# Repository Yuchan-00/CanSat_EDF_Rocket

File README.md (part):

<h1 align="center">CanSat EDF Rocket</h1>

<p align="center"><b>한국어</b> · <a href="README.en.md">English</a></p>

<p align="center">
  90 mm 덕티드팬(EDF) 하나로 캔위성을 싣고 올라가는 3D 프린트 발사체,<br>
  그리고 같은 추진 모듈로 만든 가벼운 수직 이착륙(VTOL) 기체
</p>

<p align="center">

  <br>
  <sub>왼쪽: 로켓 구성(탄도 발사 + 캔위성 사출) · 오른쪽: VTOL 배터리 구성. CadQuery 형상을 PyVista(VTK)로 그린 렌더(색은 화면용), 2026-11-04.</sub>
</p>

로켓은 수직으로 올라가 모터를 끄고, 정점에서 노즈콘을 열어 캔위성을 내보낸 뒤 자체 낙하산으로 내려옵니다.
VTOL은 같은 추진·흡입 모듈에 짧은 전자부를 얹은 시험용 기체로, 배터리·유선·하이브리드 세 가지 전원 구성이 있습니다.
**2026-11-05 사용자 결정: 앞으로 배터리 구성만 씁니다.** 유선·하이브리드는 지우지 않았지만 캐리어 PCB rev 2c의 로직 배터리(1S, 6S 팩 −x 면)와 상단 캡 스위치로는 더 맞추지 않습니다. 로직 전원 부품의 질량은 사용자가 나중에 정합니다(`configs.vtol.logic_power.in_flight_mass_model` = false; [docs/v0.9_하드웨어_변경.md](docs/v0.9_하드웨어_변경.md) 19장).
자세는 배기구의 베인 4개(MG90S 직접 구동)로 잡고, 비행 계산은 모두 ATmega128A 칩 4개가 합니다.

> **실물 비행·추력 시험 전입니다.** 아래 숫자는 CAD, 슬라이서, 시뮬레이션에서 나온 값입니다.

## 한눈에 보기

| 항목 | 값 | 종류 | 근거 |
|---|---|:-:|---|
| 로켓 구성 질량 | **2,599.2 g** | M | `cad/exports/cadquery_report.json` |
| VTOL 질량 (배터리 / 유선 / 하이브리드) | **1,653.7 / 1,405.8 / 1,526.8 g** | M | `cadquery_report_vtol*.json` |
| 몸통 | Ø120 mm, 벽 1.2 mm | 설계 | `params.json` `body` |
| 높이 (로켓 / VTOL 배터리 / 유선·하이브리드) | 856.3 / 492.5 / 500.3 mm (발사대 제외; VTOL 배터리는 2026-11-05 스위치 보호 칼라 포함) | 설계 | CadQuery 보고서 `vehicle_h_mm` |
| 추진 | 90 mm 12엽 EDF, 6S, 100 A ESC | 부품 | [예산안](docs/budget/예산안.md) |
| EDF 추력 | 2.14–3.09 kgf (22.2 V) - **아직 재지 않음** | A | 3.09 = 판매자 추력표(대리값), 2.14 = 설계 하한(배터리 VTOL T/W 1.3), `params.json`. 판정 기준 안에서 날려면 약 2.6 kgf 이상 필요([결과 문서](docs/v0.9_시뮬레이션_제어_결과.md)) |
| 비행 컴퓨터 | ATmega128A × 4 (NAV · FCU · COM · GNS), 16 MHz, 250 Hz 제어 틱 | 설계 | `params.json` `flight_computer` |
| 예산 (로켓 / VTOL 배터리) | 421,232원 / 375,192원 | M + A | 2026-10-13 판매가, 추정 줄 일부 ([로켓](docs/budget/예산안.md), [VTOL](docs/budget/예산안_vtol.md)) |
| 출력 시간 (로켓 / VTOL) | 47 h 29 min / 34 h 46 min | M + A | Bambu Studio 슬라이스, 로고 퍼지량은 가정값 ([임시 출력 계획](cad/exports/print/provisional_v09_cadquery/print_plan_provisional.md): CadQuery STL 슬라이스, Fusion 실행 전) |

<sub>M = 도구로 잰 값(CadQuery, 슬라이서) · E = 추정 · A = 가정(아직 재지 않은 입력) · 설계 = `params.json` 입력값 · 부품 = 예산안의 구매 부품 사양. 질량은 출력 부품을 슬라이서 값으로 넣은 CAD 합계이고, 일부 전자부품 질량은 가정값입니다. 로켓 출력 시간은 발사대 포함.</sub>

## 갤러리

|  |  |  |  |
|:-:|:-:|:-:|:-:|
| <sub>로켓 · 2,599.2 g</sub> | <sub>VTOL 배터리 · 1,653.7 g</sub> | <sub>VTOL 유선 · 1,405.8 g</sub> | <sub>VTOL 하이브리드 · 1,526.8 g</sub> |

|  |  |
|:-:|:-:|
| <sub>로켓 구성: 외관과 1/4 잘라낸 내부 (캔위성 350 g, 낙하산, EDF, 배터리)</sub> | <sub>VTOL 구성: 낙하산·캔위성을 빼고 짧은 전자부를 얹은 기체</sub> |
|  |  |
| <sub>직접 구동 베인 단면: 서보 축과 베인 축이 한 선 위, 나사 없는 혼 소켓</sub> | <sub>같은 베인의 분해도</sub> |
|  |  |
| <sub>모터 전원선 통로 단면 (시계 장착, 몸통 밖 블리스터)</sub> | <sub>통로의 여유 범위: 재지 않아도 맞게 설계한 범위 (출구 각도 0–360°, 선 지름 3.6–4.3 mm)</sub> |
|  |  |
| <sub>로켓 옆모습: 로고는 전자부 모듈 양쪽(67° / 293°)</sub> | <sub>유선 전원 준비형 VTOL (배터리 없는 유선, 하이브리드)</sub> |

<sub>모든 그림은 CadQuery 형상의 렌더입니다. 전자부품은 외곽 상자로, 선·폼·나사 일부는 그림용으로 그렸습니다.</sub>

## YUCHAN 로고

<p align="center">
  <br>
  <sub>① 후보 4개 - 왼쪽 위부터 launch, extended, retro, patch. 사용자가 <b>launch</b>를 골랐습니다.</sub>
</p>
<p align="center">
  <br>
  <sub>② 기체 축을 따라 세로로 넣도록 다듬은 최종 모양 (펼친 크기 121.0 × 18.4 mm)</sub>
</p>
<p align="center">
  <br>
  <sub>③ 다듬기 전(위)과 후(아래) 확대 비교, 2 mm 격자</sub>
</p>

|  |  |
|:-:|:-:|
| <sub>④ 기체 위: 로켓 전자부 모듈 양쪽</sub> | <sub>④ 기체 위: VTOL 전자부 모듈 양쪽</sub> |

* **찍는 방법**: P2S + AMS 2색 상감. 흰 몸통(PLA Matte Ivory White 11100)의 바깥 벽 한 줄(0.42 mm)만 주황(Mandarin Orange 11300)으로, 튀어나오지 않습니다.
* **자리**: 전자부 모듈 방위 67° / 293°, 아래에서 위로 읽음. 형상 검사 C36 PASS (창·슬롯·구멍에서 3 mm 이상, 가장 가는 획 2.20 mm).
* **AMS 비용 (슬라이서 M, 퍼지량 150 / 210 mm³는 가정 A)**: 색 바꿈 576번, 출력 +14 h 23–26 min, 버리는 양 180.4 g.
* 자세한 내용: [하드웨어 변경 문서 18장](docs/v0.9_하드웨어_변경.md), [제작 가이드 2장](docs/제작가이드.md).

## 개발 과정

**v0.6.3 → v0.8.1 (2026-10-13 ~ 10-21)** - 예산판 로켓을 Fusion 360 스크립트와 CadQuery 두 프로그램으로 따로 모델링해 서로 확인했습니다. v0.8.1에서 GPS 위치 유지를 맡는 네 번째 칩(GNS)을 더했습니다.

|  |  |
|:-:|:-:|
| <sub>Fusion 360 스크립트 v0.6.3 실행 결과 (2026-10-20, 컴포넌트 41개)</sub> | <sub>v0.8.1 GNS 보드 배치 (CadQuery 트윈 그림)</sub> |

**v0.9 (2026-10-28)** - 가벼운 VTOL 구성, 직접 구동 베인, 제어 라운드(C1–C7), 검토 수정 라운드(F1–F10)와 유선 전원 규칙(T1–T6). 바뀔 때마다 이전 / 이후를 같은 조건의 시뮬레이션으로 나란히 비교했습니다.

<p align="center">
  <br>
  <sub><b>시뮬레이션 (실제 비행 영상 아님), 2배속.</b> 같은 강한 소용돌이 바람에서 v0.8.1 로켓 적층(왼쪽)은 회전이 커져 비상정지하고 낙하산을 펼치고, v0.9 VTOL(오른쪽)은 계속 비행합니다.
  기체·시뮬레이션 모델·제어가 모두 달라서 차이 전부를 제어 변경의 효과로 볼 수는 없습니다. 영상 속 기체는 흰색 도색 전의 검정판이고, 질량은 영상을 만들 때의 값입니다.</sub>
</p>

<p align="center">
  <br>
  <sub><b>시뮬레이션, 실시간.</b> 배터리 없는 유선 VTOL이 실내에서 1.5 m까지 떠올라 호버링합니다. 사람 모형은 크기 비교용입니다. 영상 속 기체는 흰색 도색 전의 검정판입니다.</sub>
</p>

**모터선 통로 (2026-10-28 ~ 11-04)** - 처음 두 판은 모터선 출구를 가정했고, 10-29에 실물 사진으로 출구를 확인했습니다. 11-03에는 어느 각도로 나와도 재지 않고 맞는 설계로 바꿨습니다: EDF를 돌려 선 묶음을 통로 하나에 맞추고, 장착 탭은 둘레의 키웨이 25개 중 가까운 곳에 들어갑니다(시계 장착).

<p align="center">
  <br>
  <sub>왼쪽부터 10-28 처음 → 10-28 수정 → 10-29 실물 사진 기준 출구 → 시계 장착(11-03 설계, 11-04 수정 라운드 뒤, 검정) → 11-04 흰색. 1/4 잘라낸 단면.</sub>
</p>

|  |  |
|:-:|:-:|
| <sub>실물 EDF (2026-10-29): 모터선 묶음이 나오는 자리를 이 사진으로 정했습니다</sub> | <sub>흰색 도색 직전의 로켓 (2026-11-04 오전, 검정 PLA). 위 갤러리가 지금 모습입니다</sub> |

## 아비오닉스 캐리어 PCB와 로직 전원 (2026-11-04 ~ 11-05)

VTOL의 칩 4개, 센서, 무선, 로거를 한 장에 올린 캐리어 PCB를 KiCad 10(kicad-cli)과 Freerouting으로 만들었습니다. **만들거나 전원을 넣어 본 적은 없습니다(NOT_VERIFIED).**

|  |  |
|:-:|:-:|
| <sub>캐리어 PCB rev 2c: 76 × 70 mm 4층, ATmega128A × 4, ESP-12E (kicad-cli 렌더)</sub> | <sub>같은 보드 윗면 (kicad-cli 렌더)</sub> |

<p align="center">
  <br>
  <sub>회로도 8장 (전원, NAV, FCU, COM, GNS, 레벨 시프터, 커넥터, 최상위)</sub>
</p>

* **검사 (M, kicad-cli 10.0.6)**: ERC 오류 0 · 경고 0, DRC 오류 0 · 경고 0 · 미연결 0 · 회로도 불일치 0. 부품 162개(실장 152), 넷 100개.
* **사용자가 정한 부품**: BMP280, GY-521, NEO-7M(리드만), 무선 ESP-12E(LoRa PLM100 대신, 2026-11-05), 로직 배터리 1S 4200 mAh(디바이스마트 16021596). 부품은 모두 JLCPCB(LCSC) 또는 디바이스마트에서 찾은 것만 썼습니다.
* **고쳐 온 과정**: rev 1(PLM100 + 2S, 2층)은 독립 검토에서 디커플링·크리스털·실크·GND 문제가 나와 다시 만들었습니다. rev 2는 2층으로는 배선이 끝나지 않아(미연결 63) 4층으로 바꿨고, 쓰지 않는 5번째 칩 자리를 뺐습니다. rev 1은 [`pcb/vtol_carrier/archive/`](pcb/vtol_carrier/archive/)에 있습니다.
* **로직 전원 (CAD)**: 1S 팩은 6S 팩 −x 면(A 자리), 스위치(MTS-102)는 상단 캡에 달고, 레버 둘레에 캡과 한 몸으로 출력하는 보호 칼라를 둡니다(검사 C37–C41). 로직 전원 부품 약 94 g은 사용자가 정할 때까지 비행 질량에 넣지 않았습니다(넣으면 1,747.7 g, T/W 1.23 (E)).
* **Wi-Fi 거리**: ESP-NOW 1 Mbps + 지상국 외부 안테나로 늘립니다(계산 E). 비행 전에 1 km 이상 지상 통신 시험이 필요하고, 실패하면 LoRa로 돌아갑니다.
* 자세한 내용: [PCB README](pcb/vtol_carrier/README_ko.md), [하드웨어 변경 19장](docs/v0.9_하드웨어_변경.md), [제작 가이드 3장 14단계](docs/제작가이드.md).

|  |  |
|:-:|:-:|
| <sub>로직 전원: 1S 팩(A 자리)과 스위치 선 (칼라 넣기 전 그림)</sub> | <sub>상단 캡 스위치 보호 칼라: 레버 두 끝 자세보다 2.14 mm 높음 (M)</sub> |

## 검증 방식

설계값은 한 곳(`params.json` → `cad/layout.py`)에서 나오고, 합격·불합격은 정해진 도구와 기준으로 판정합니다.

* **형상 검사 C1–C41** (CadQuery): 네 구성 모두(C37-C40 로직 전원, C41 스위치 보호 칼라는 VTOL 배터리만, 나머지 N/A). FAIL / WARN - 로켓 0 / 5, VTOL 배터리 0 / 3(2026-11-05 보호 칼라로 C39 레버 WARN이 PASS가 됨), 유선 1 / 2, 하이브리드 1 / 2.
* **Fusion 360 교차 확인**: 같은 사양을 Fusion 스크립트로도 만듭니다. 이번 라운드는 스크립트 모의 실행(재생)으로 CadQuery 형상과의 불리언 차이를 봤습니다(로고 0.0000 mm³). Fusion GUI 실행(0.9.6)은 아직 사람이 해야 합니다.
* **슬라이스**: Bambu Studio CLI로 실제 슬라이스하고 무게·시간·색 바꿈 수를 G-code에서 셉니다.
* **6자유도 시뮬레이션 + 캠페인**: 현장 조건 500회에서 통과 18 %, 비상정지 13 % ([결과 문서](docs/v0.9_시뮬레이션_제어_결과.md)).
* **4칩 공동 시뮬레이션** (simavr): NAV · FCU · COM · GNS 펌웨어를 명령어 단위로 함께 돌립니다. 합격 기준 22개 모두 통과(2026-10-29, [펌웨어 결과](docs/v0.9_펌웨어_결과.md)). 11-04에 헤더를 다시 만들어서 21행(탄도 이미지 해시)은 새 해시로 사용자 재선언을 기다립니다([하드웨어 변경 18.8](docs/v0.9_하드웨어_변경.md)).
* **펌웨어 라운드 (2026-11-06)**: 기체 무선을 ESP8266 Wi-Fi(ESP-NOW 브리지, [firmware/esp_bridge](firmware/esp_bridge/README.md))로 바꿨습니다. VTOL과 로켓 모두이고, LoRa는 예비로 남습니다. 헤더를 다시 만들고 모든 HEX를 다시 빌드했습니다. 제어는 바꾸지 않았습니다. 합격 기준 22개 중 20개 통과, 19번은 이번에 판정 안 함, 21번은 새 해시로 사용자 재선언 대기입니다(M, 시뮬레이터). ESP8266 펌웨어는 arduino-cli와 코어 `esp8266:esp8266` 3.1.2로 컴파일했습니다. 변형 5개 모두 성공했고, 굽지는 않았습니다(M, [펌웨어 결과 11.10절](docs/v0.9_펌웨어_결과.md)).
* **독립 검토**: 라운드마다 다른 검토자가 복사본에서 다시 돌려 결함을 찾고, 고친 것과 남긴 것을 문서에 적습니다.

> **아직 열려 있는 것**
> * EDF 추력을 재지 않았습니다. 실물 출력·조립·비행, 실제 칩 측정도 아직 없습니다.
> * C33 옆 치우침: 유선 **FAIL 14.0 %**, 하이브리드 **FAIL 11.2 %** - 무게중심 이동 등 사용자 결정.
> * 가벼운 VTOL 기체의 시나리오 시험 5개가 원래부터 실패합니다(2026-11-04 pytest, [하드웨어 변경 17.9](docs/v0.9_하드웨어_변경.md), [펌웨어 결과](docs/v0.9_펌웨어_결과.md) 6장).
> * AMS 퍼지량 150 / 210 mm³는 가정값입니다. 긴 출력 전에 짧은 2색 시험 출력이 필요합니다.

## 폴더 구조

| 경로 | 내용 |
|---|---|
| [`cad/`](cad/) | 레이아웃(`layout.py`), Fusion 360 스크립트, CadQuery 트윈 + 형상 검사, 로고(`livery/`), 출력 파일 |
| [`sim/`](sim/) | 6자유도 비행 시뮬레이션, 기체 감독 로직·링크 기준 구현, 게인 튜닝, 캠페인 |
| [`firmware/`](firmware/) | ATmega128A 4칩 펌웨어(avr-gcc), 지상 브리지, simavr 공동 시뮬레이션 |
| [`sizing/`](sizing/) | 질량·추력·에너지·안정성·강도 산정 |
| [`tools/`](tools/) | 지상국, 출력 파일 생성, 예산, 시뮬레이션 영상 도구 |
| [`docs/`](docs/) | 사양서, 변경 문서, 제작 가이드, 예산, 시험·안전·법규 |
| [`render/`](render/) | Blender 렌더 파이프라인 (시뮬레이션 영상용) |
| [`pcb/`](pcb/) | VTOL 캐리어 PCB: KiCad 프로젝트, 생성 스크립트, 거버·BOM·CPL, 검사 보고서 |

<sub>`sim/out/`과 STL · STEP · F3D 파일은 만들어지는 파일이라 저장소에 없습니다. 다시 만드는 방법은 아래 기술 상세에 있습니다.</sub>

## 라이선스

[CC BY-NC 4.0](https://creativecommons.org/licenses/by-nc/4.0/) - 출처를 밝히면 비상업적 목적으로 공유·수정할 수 있습니다. 자세한 내용은 [LICENSE](LICENSE). 다른 사람의 자료는 각자의 라이선스를 따릅니다([render/assets/CREDITS.md](render/assets/CREDITS.md)).

<sub>README의 그림은 모두 기존 렌더·사진·영상을 자르거나 줄인 복사본입니다. 출처와 sha256: [docs/images/SOURCES.md](docs/images/SOURCES.md)</sub>

---

## 기술 상세 (원래 README)

<sub>아래는 기존 README 내용 그대로입니다. 날짜가 적힌 문단은 그 시점의 기록입니다.</sub>

# CanSat EDF Rocket — 덕티드팬 추진 캔위성 발사체

캔위성을 싣고 수직으로 올라간 뒤, 모터를 끄고 정점에서 노즈콘을 분리해 캔위성을 내보내고, 기체는 자체 낙하산으로 내려오는 발사체입니다.
추진은 90 mm 전기 덕티드팬(EDF) 1개, 자세 제어는 배기구의 베인 4개(MG90S 서보)로 합니다.
비행 계산은 모두 **ATmega128A**(v0.6.3: NAV·FCU·COM 3개, v0.8.1부터 GNS를 더해 4개)가 하고, 구조물은 전부 <b>Bambu Lab P2S + PLA Matte 흰색(Ivory White)</b>으로 출력하고, 전자부 모듈 양옆에 주황(Mandarin Orange) **YUCHAN** 로고를 AMS 2색 상감으로 넣습니다(2026-11-04; 발사대는 검정).

기본 설계는 **예산판 `BUDGET_90mm_6S`** (캔위성 제외)이고, 현재 판은 **v0.9** (2026-10-28)입니다. 아래 표와 "검증 방법"의 숫자 중 날짜가 2026-10-16 이전인 것은 v0.6.3 로켓 기준 값입니다.
처음 설계(KAIST 1 kg 캔위성, 12S)는 `params.json`의 `KAIST_90mm_12S` 프리셋으로 그대로 남아 있습니다.

## 현재 상태 (v0.9, 2026-10-28)

* **하드웨어 v0.9**: 직접 구동 베인, 가벼운 **VTOL 구성**(배터리 1,653.6 g, 배터리 없는 유선 1,405.7 g, 하이브리드 1,526.7 g; 낙하산·캔위성 없음). 로켓 구성은 2,599.1 g. **2026-11-03 모터선 통로를 "재지 않아도 맞게" 바꿨습니다(시계 장착)**: EDF를 돌려 선 묶음을 0°의 통로 하나(몸통 밖 블리스터)에 맞추고, 탭은 둘레의 키웨이 25개 중 가까운 곳에 들어갑니다(탭 나사 없음; 2026-11-04 수정 라운드: 키웨이 사이 이빨이 모터 토크를 탭 하나로 받아도 안전율 5.9, 선은 먼저 굽히고 EDF를 내림). 공장 수축 튜브 그대로, 출구 각도 0-360°, 선 지름 4.3 mm, 굽힘 7-15 mm까지 받고 모든 경우의 겹침이 0 mm³입니다(C29, C34). 무게 목표(1,650 / 1,400 g)는 3.6 / 5.7 g 넘습니다. 옆 치우침 검사 C33(선 항력 포함, 나쁜 쪽 방위·Cd): 유선 **FAIL 14.0 %**, 하이브리드 **FAIL 11.2 %**, 배터리 WARN 7.7 %, 로켓 WARN 5.7 % - 무게중심 이동 등 사용자 결정. 출력 전에 잴 것은 없습니다(조립한 그대로의 추력 시험만 필요). 비행 컴퓨터는 ATmega128A 4개(NAV·FCU·COM·GNS, v0.8.1부터). 자세한 내용: [docs/v0.9_하드웨어_변경.md](docs/v0.9_하드웨어_변경.md) 17장.
* **흰색 몸통 + YUCHAN 로고 (2026-11-04)**: 기체 출력 부품을 모두 흰색(Bambu PLA Matte Ivory White, 11100)으로 바꾸고, 전자부 모듈 양옆(67° / 293°)에 주황(Mandarin Orange, 11300) 세로 로고를 평평한 2색 상감(바깥 벽 한 줄, 0.42 mm)으로 넣었습니다. 로켓·VTOL 모두. 새 검사 C36 PASS(창·슬롯·구멍·끝에서 3 mm 이상, 획 2.20 mm). AMS 비용(슬라이서 M, 퍼지량 150/210 mm³는 가정값 A): 색 바꿈 576번, +14 h 26 min, 버리는 양 180 g. 주황은 한 번만 지나가게 찍습니다(얇은 벽 감지, 독립 검토 F1). 무게: VTOL 배터리 1,653.7 g, 유선 1,405.8 g, 하이브리드 1,526.8 g, 로켓 2,599.2 g. 자세한 내용: [docs/v0.9_하드웨어_변경.md](docs/v0.9_하드웨어_변경.md) 18장, 출력 방법: [docs/제작가이드.md](docs/제작가이드.md) 2장.
* **시뮬레이션·제어 v0.9 (Python 기준 코드만)**: VTOL 기체에 맞춘 자세 게인, 이륙·착지 제어, 유선 전원 규칙, 독립 검토 반영. 처음 쓴 표본(FRESH2)에서 현장 120회 통과 5 → 22, 비상정지 26 → 17. 새 표본 캠페인 현장 500회: 통과 18 %, 비상정지 13 %. 결과 문서: [docs/v0.9_시뮬레이션_제어_결과.md](docs/v0.9_시뮬레이션_제어_결과.md).
* **EDF 추력은 아직 측정하지 않았습니다.** 시뮬레이션은 22.2 V 기준 2.14~3.09 kgf를 가정합니다. 판정 기준 안에서 날려면 약 2.6 kgf 이상(최소 2.46 kgf)이 필요합니다.
* **남은 큰 위험**: 잔류 회전이 로터와 반대 방향일 때 비상정지, 시연 밀기(5~15 N) 불가(안전 약 3 N 이하), 이륙 초과 상승(유선 최대 약 1.3 m → 도르래 4.5 m 이상).
* **펌웨어 (2026-11-09 갱신)**: v0.9 제어 변경의 C 이식과 4칩 공동 시뮬레이션은 2026-10-29 펌웨어 라운드에서 끝났습니다. 2026-11-06 라운드에서 헤더를 다시 만들고 ESP Wi-Fi 링크를 넣었습니다. 합격 기준 22개 중 20개 통과, 21번(탄도 이미지 해시)은 사용자 재선언 대기입니다([펌웨어 결과](docs/v0.9_펌웨어_결과.md) 11장). 처음 쓴 이 줄("펌웨어는 아직 v0.8.1")은 2026-10-28 기준이었습니다.
* **파이썬 시험 (2026-10-28, 프로젝트 전체)**: 1,097 통과, 58 실패, 15 오류, 8 건너뜀, 2 예상 실패. 실패·오류 73개 중 67개는 헤더 생성기가 새 제어 키를 거부해서(펌웨어 라운드), 1개는 지상 브리지 헤더 STALE, 1개는 원래 있던 시험, 4개는 가벼운 기체의 VTOL 시나리오 시험입니다(이유: 결과 문서 10장).

## 조종 방식 (v0.4, 비행 컴퓨터 v0.6.3)

* **기체 안에서는 자세 제어만 합니다.** 비행 컴퓨터는 ATmega128A 4개로 나뉩니다(v0.6.3에 3개, v0.8.1에 GNS를 더해 4개).
  * **NAV**: MPU-6050과 기압계를 읽고 자세 추정과 고도 필터를 돌립니다. 기압계 부품은 BMP280 모듈입니다(사용자 결정 2026-11-04, GY-63 MS5611 대신). 펌웨어의 기본 기압계 드라이버도 BMP280입니다(2026-11-10 제어 라운드, `flight_computer.nav.baro_sensor`). MS5611 드라이버는 빌드 옵션(`nav_ms5611`)으로 남아 있습니다. BMP280 드라이버의 설정값은 데이터시트 값(A)이고, 실제 부품으로는 아직 재지 않았습니다. 매 틱(250 Hz) 72바이트 항법 프레임을 SPI(nlink)로 FCU에 보냅니다.
  * **FCU**: 기체 감독 로직(명령, 안전 인터록 I1–I10), 자세 제어, 서보·ESC 펄스, 로그. 비행 판단은 모두 여기서 합니다. 항법 프레임이 들어오면 틱을 시작하고, 4.6 ms 안에 오지 않으면 자체 타이머로 돌며 그 틱의 센서를 고장으로 봅니다.
  * **COM**: 무선, 명령 해독, FCU가 보낸 스냅숏으로 텔레메트리 작성. FCU와 UART(ilink, 250 kbaud)로 연결합니다. 무선은 2026-11-06부터 ESP-12E(ESP-NOW Wi-Fi)가 기본이고 LoRa는 예비입니다.
  * **GNS** (v0.8.1부터): GPS(NEO-7M) 해석과 위치 유지 제어. NAV와 UART(glink, 250 kbaud)로 연결합니다.
  * NAV, COM, GNS는 비행 판단을 하지 않습니다. 안전 인터록은 어떤 명령으로도 끌 수 없습니다.
  * 근거: `params.json` `flight_computer`, `firmware/atmega128_fc/src/core/nlink_proto.h`, `ilink_proto.h`.
* **발사·모터 정지·노즈 분리는 지상국이 무선(기본 ESP-NOW, 예비 LoRa)으로 명령합니다.** 노트북의 `tools/ground_station.py`가 초당 2번 기체에 묻고, 기체는 그때만 텔레메트리로 답합니다.
* 지상국의 **어시스트 모드**(기본 켜짐)가 목표 고도에서 CUT, 정점에서 RELEASE를 자동으로 보냅니다. v0.6.3부터는 응답이 안 온 순간(응답 대기 시간 초과)에도 마지막 텔레메트리를 그 나이만큼 앞으로 늘려 같은 규칙으로 판단합니다. 운용자가 언제든 직접 명령하거나 끌 수 있습니다.
* 링크가 끊기거나 느려도 기체가 스스로 안전하게 끝냅니다. 패드에서 2초 끊기면 SAFE, 비행 중 3초 끊기면 모터를 끄고 낙하산을 펼칩니다. 예상 정점이 150 m에 닿으면 모터를 끄고(I4), 사출 명령 없이 떨어지면 스스로 사출합니다(I6). NAV가 비행 중 리셋되면 자세를 잃은 것으로 보고 ABORT합니다(I9).
* 예비 LoRa를 쓸 때는 두 종류의 모듈을 지원합니다. UART형(Ebyte E22/E220/E32)은 그대로 연결하고, SPI형은 **900 MHz SX1276 모듈**(RFM95W, Ra-01H)이어야 합니다. Ra-01/Ra-02는 433 MHz라 맞지 않습니다. SPI형은 지상 쪽에 아두이노 나노 브리지(`firmware/ground_bridge/`)가 필요합니다.

사용법은 [지상국_사용법.md](docs/지상국_사용법.md), 배선은 [firmware/README.md](firmware/README.md)에 있습니다.

| 항목 | 값 | 근거 |
|---|---|---|
| 예산 | 342,082원 (모두 새로 구입). ATmega128 보드 1개와 나사를 보유하면 319,014원. 추정가(ASSUMED) 7줄 합 22,000원: 서보 연장선 7,000, 4 mm 총알 커넥터 5,000, 낙하산 줄 3,000, 사출 스프링 3,000, ilink·nlink 배선 각 1,500, 분압 저항 1,000 | `docs/budget/예산안.md` (2026-10-13 판매가, 링크 포함) |
| 충전기·ISP가 없으면 | +38,500원 | 같은 문서 |
| LoRa 모듈 종류에 따라 지상 쪽 | 최대 +7,761원 (USB-UART 변환기 또는 나노 브리지, 추정가) | 같은 문서 |
| 실을 수 있는 캔위성 | 국제 규격 Ø66 × 115 mm, 350 g | 예산 내 추력 약 3 kg의 한계 |
| 동체 | 외경 120 mm, 벽 1.2 mm, 전장 856 mm | `cad/layout.py` |
| 비행 컴퓨터 | ATmega128A 3개, 16 MHz, 250 Hz. NAV 보드는 트레이(예전 FC 자리), FCU 보드는 흡입 모듈 격벽 위에 폼 테이프 3 mm + 케이블 타이, COM 보드는 페이로드 격벽 아래 보스 4개에 M3×5. 무선·로거 상자(LoRa 모듈, OpenLog, 레벨 시프터, AMS1117)는 COM 옆 격벽 아래 | `params.json` `electronics`, `payload_module.com_mount`; 형상 검사 C22, C24, C25 |
| 이륙 질량 | CAD 2.59 kg (2585.7 g, 출력물 1029 g). 크기 산정의 비행 질량 2.60 kg (2595.7 g, 스프링·피스톤 부속 나머지 10 g 포함) | CadQuery 질량 보고서 (Fusion 360과 0.003 % 일치), `sizing/sizing_report.md` |
| 추진 | Hobbyocean 90 mm 12엽 EDF 6S, 100 A ESC, 6S 2200 mAh | |
| EDF 고정 (2026-11, 시계 장착) | EDF의 장착 탭 2개를 둘레의 키웨이 25개 중 가까운 곳에 넣음(탭 나사 없음). 위는 흡입부 선반, 아래는 탭 밑 폼 패드와 3 mm 바닥 패드. 모터 전선은 0°(ESC 쪽) 통로 하나(블리스터)로. 치수는 판매처 도면 기준 | `docs/SPEC.md` 3.7c, `docs/v0.9_하드웨어_변경.md` 17장 |
| 서보 배선 (v0.6) | 베인 서보 4개의 선: 포드 창 → 핀 옆 바깥 → 추진 모듈 안 통로 → 흡입 모듈 서보 통로 → 흡입 격벽 구멍 → 격벽 위 FCU 보드(전자 칸 맨 아래)에서 끝납니다. 연장선 길이 524 / 434 / 450 / 539 mm (서보 1–4) | `cad/layout.py`, 형상 검사 C23 |
| 추력/중량비 | 1.19 (비행 질량 2.60 kg), 1.195 (CAD 질량 2.59 kg). 대용 추력표의 공칭 30.3 N 기준. 검사 C12 경고 (통과 기준 1.30) | `sizing/sizing_report.md`, `cad/exports/cadquery_checks.md` |
| 정적 안정 여유 | 0.50–0.51 구경: 시뮬레이션 0.50, CAD 검사 C13 0.51, 크기 산정 0.51. 경고선 0.5, 권장 1.0 | `sim/out/sim_report.md`, `cadquery_checks.md`, `sizing_report.md` §6 |
| 비행 (S2) | 목표 140 m, UART형 링크 손실 5 %. 정점 144.8 m, 어시스트 CUT 122.3 m, 노즈 분리 정점 0.12 s 뒤 (v_z −1.2 m/s), 착지 6.2 m/s | 6자유도 시뮬레이션 S2 |
| S2 추가 시드, 몬테카를로 | 추가 시드 10개 모두 통과 (정점 135.2–148.7 m, 1개는 I4가 먼저 모터를 끔). 몬테카를로 20개 중 19개 통과 (1개는 분리 때 v_z −5.01 m/s로 기준 5 m/s를 넘음). 20개 모두 정점 150 m 아래 (134.6–148.3 m) | 같은 보고서 |
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
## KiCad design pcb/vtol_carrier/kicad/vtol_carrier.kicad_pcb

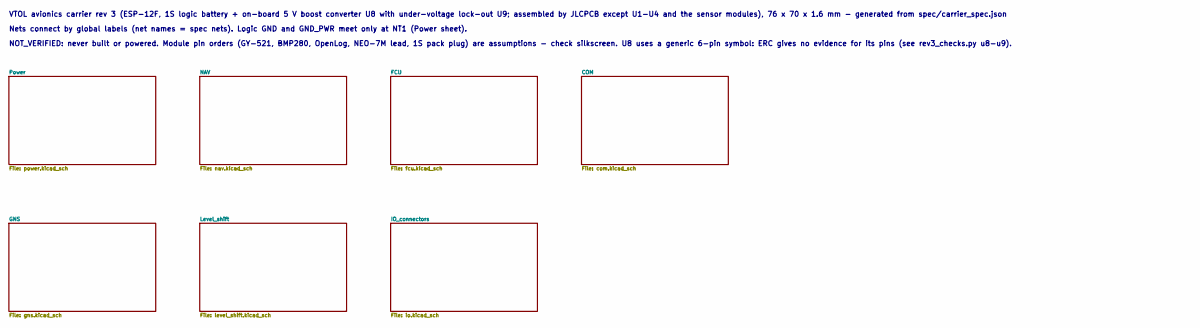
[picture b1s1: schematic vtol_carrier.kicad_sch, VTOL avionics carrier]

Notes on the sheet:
VTOL avionics carrier rev 3 (ESP-12F, 1S logic battery + on-board 5 V boost converter U8 with under-voltage lock-out U9; assembled by JLCPCB except U1-U4 and the sensor modules), 76 x 70 x 1.6 mm - generated from spec/carrier_spec.json
Nets connect by global labels (net names = spec nets). Logic GND and GND_PWR meet only at NT1 (Power sheet).
NOT_VERIFIED: never built or powered. Module pin orders (GY-521, BMP280, OpenLog, NEO-7M lead, 1S pack plug) are assumptions - check silkscreen. U8 uses a generic 6-pin symbol: ERC gives no evidence for its pins (see rev3_checks.py u8-u9).

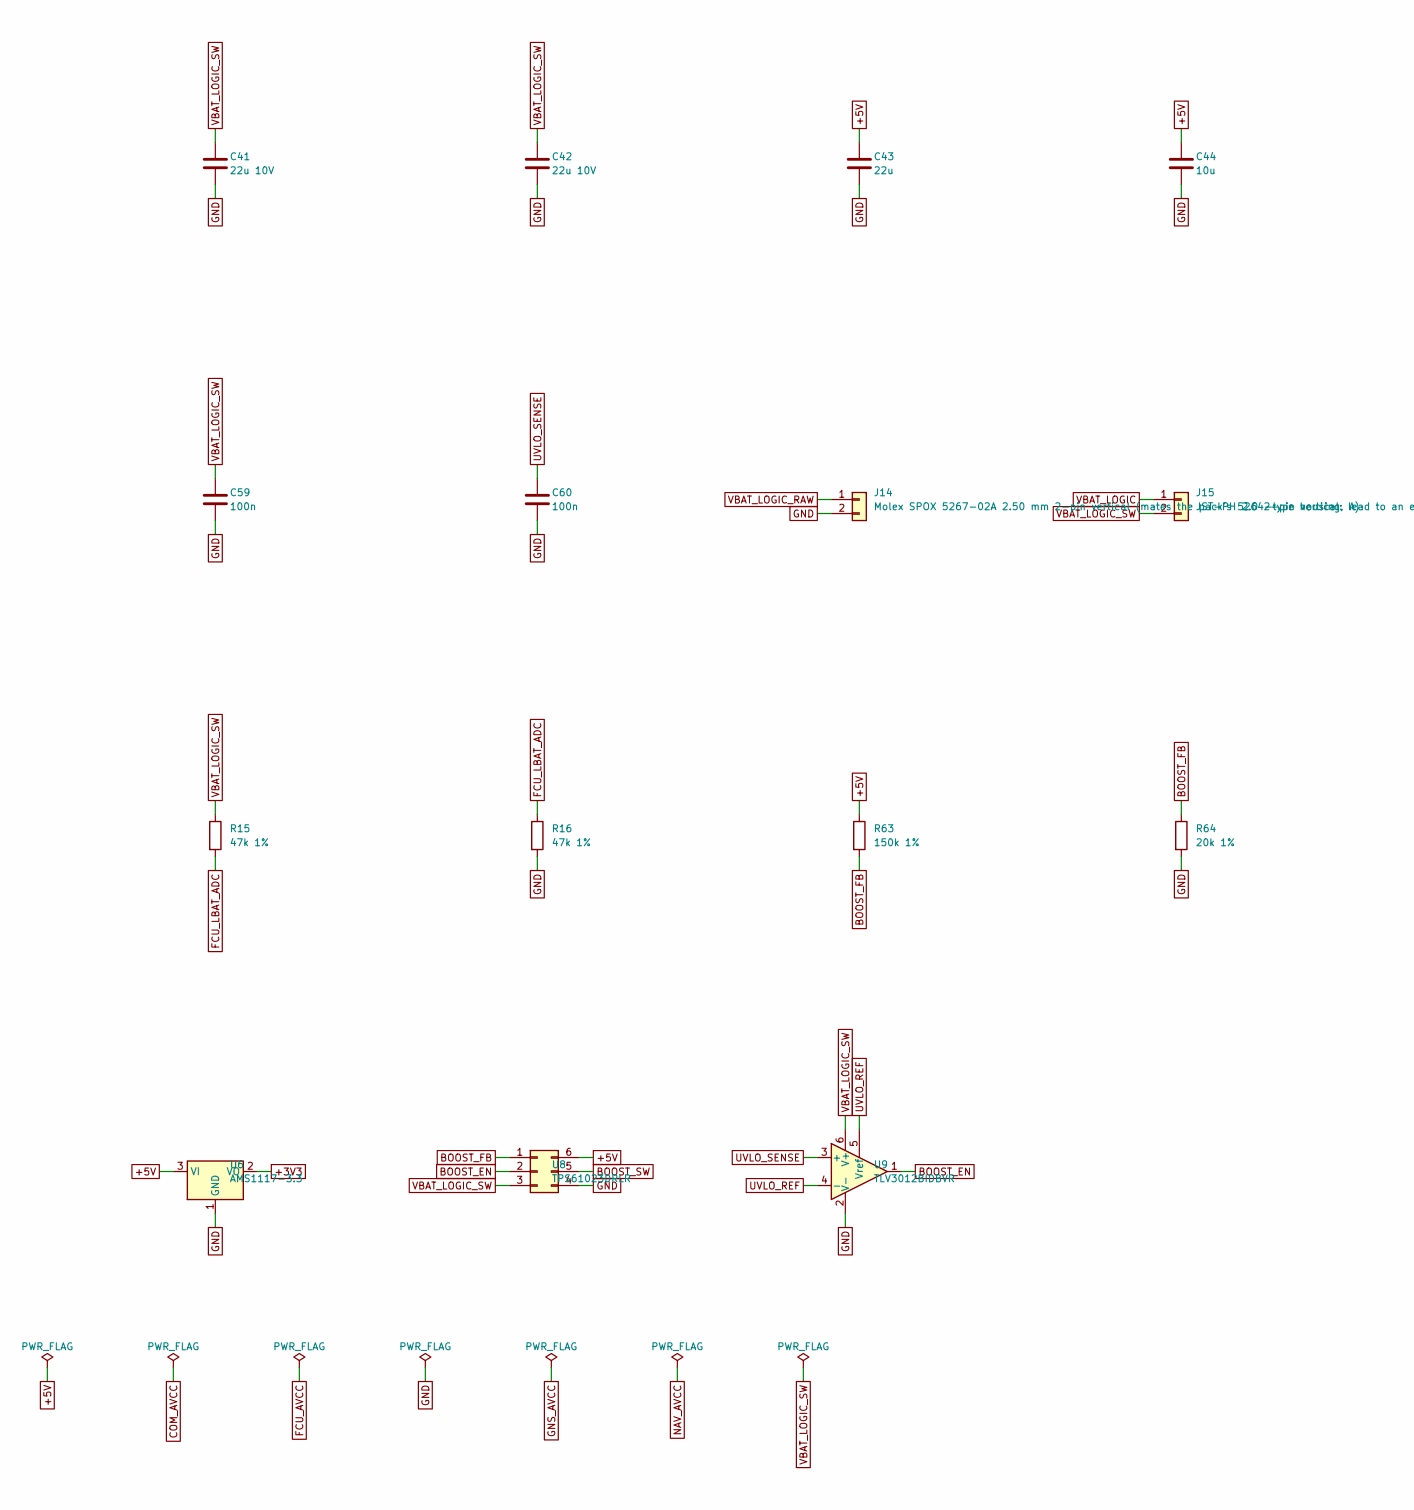
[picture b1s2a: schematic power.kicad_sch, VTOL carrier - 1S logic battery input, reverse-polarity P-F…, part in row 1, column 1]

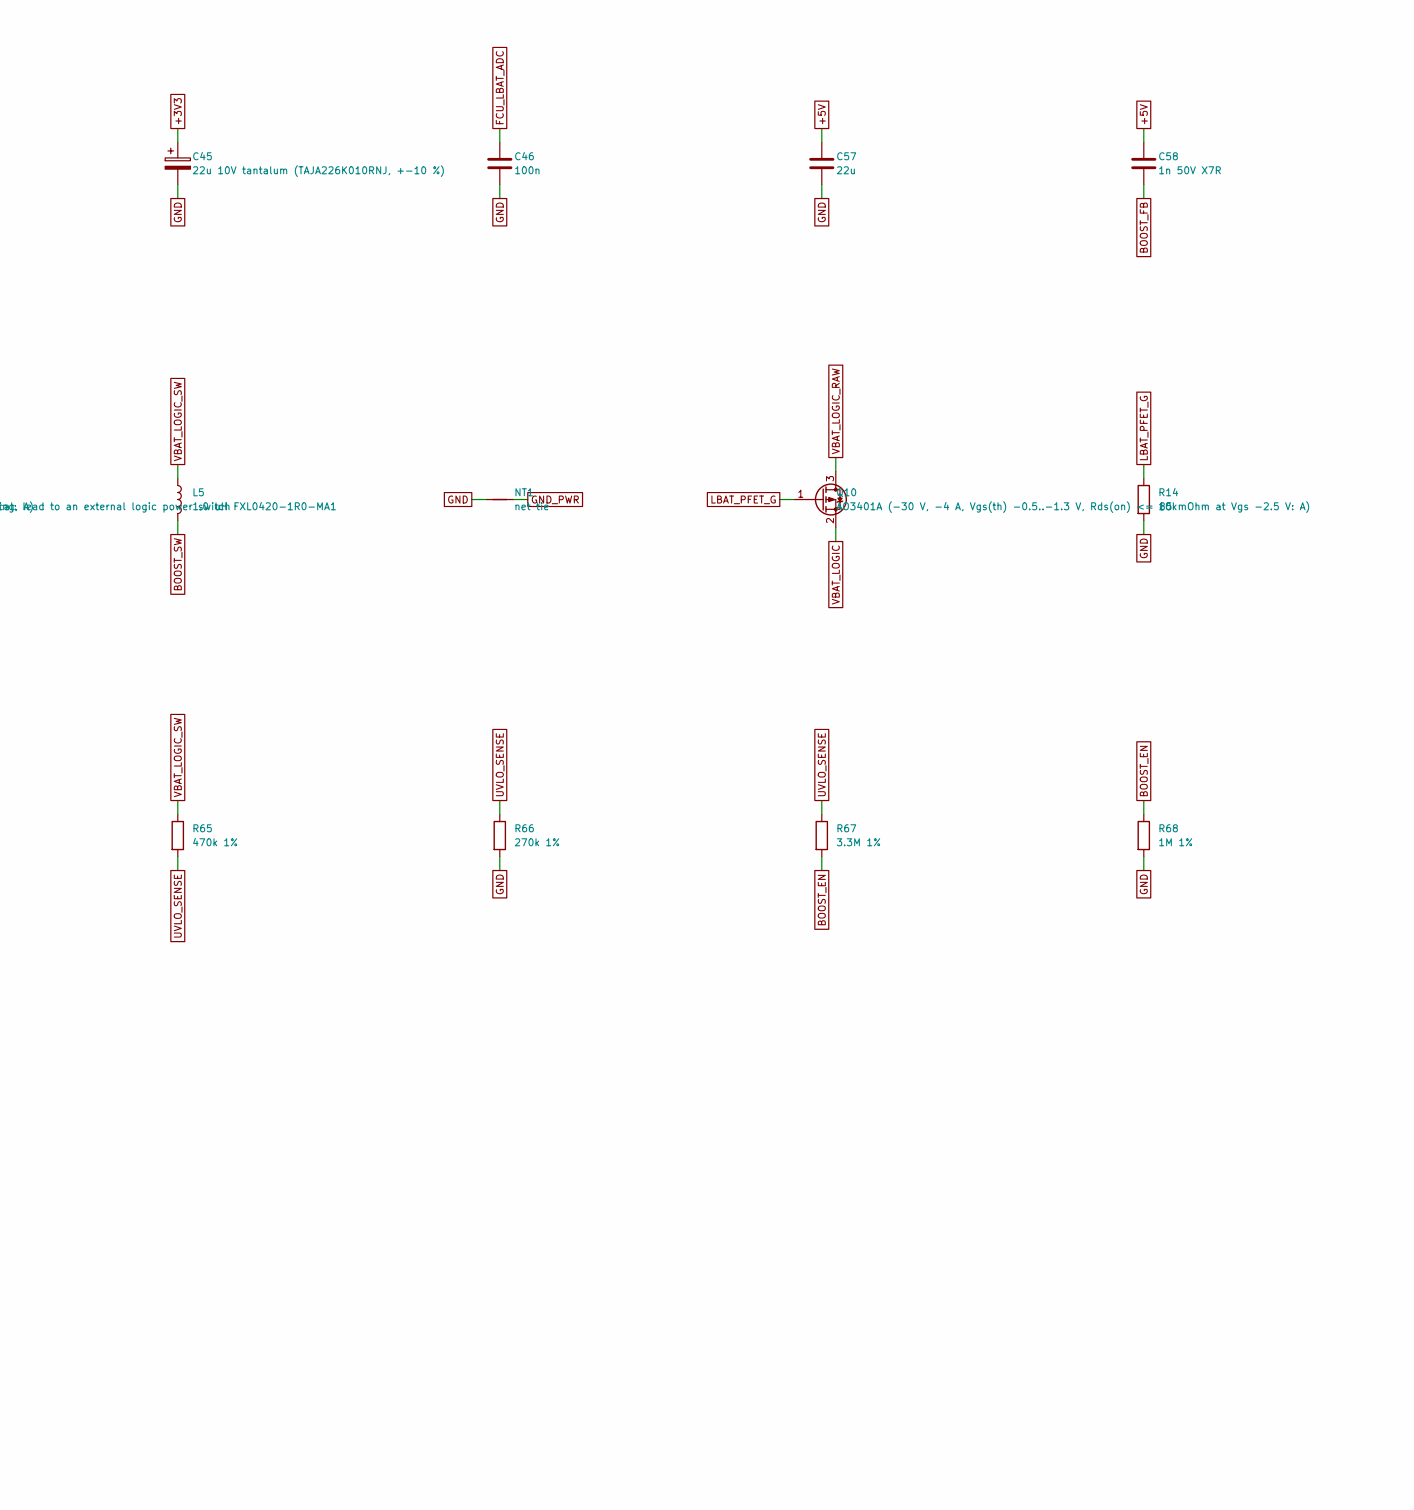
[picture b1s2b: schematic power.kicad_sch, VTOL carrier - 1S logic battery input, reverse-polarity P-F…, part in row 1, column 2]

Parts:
C41, C42: 22u 10V; C_1206_3216Metric
C43, C57: 22u; C_1206_3216Metric
C44: 10u; C_0805_2012Metric
C45: 22u 10V tantalum (TAJA226K010RNJ, +-10 %); CP_EIA-3216-18_Kemet-A
C46, C59, C60: 100n; C_0603_1608Metric
C58: 1n 50V X7R; C_0603_1608Metric
J14: Molex SPOX 5267-02A 2.50 mm 2-pin vertical (mates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; Molex_SPOX_5267-02A_1x02_P2.50mm_Vertical
J15: JST-PH 2.0 2-pin vertical: lead to an external lo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; JST_PH_B2B-PH-K_1x02_P2.00mm_Vertical
L5: 1.0 uH FXL0420-1R0-MA1; L_Changjiang_FXL0420
NT1: net tie; NetTie-2_SMD_Pad0.5mm
Q10: AO3401A (-30 V, -4 A, Vgs(th) -0.5..-1.3 V, Rds(o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; SOT-23
R14: 10k; R_0603_1608Metric
R15, R16: 47k 1%; R_0603_1608Metric
R63: 150k 1%; R_0603_1608Metric
R64: 20k 1%; R_0603_1608Metric
R65: 470k 1%; R_0603_1608Metric
R66: 270k 1%; R_0603_1608Metric
R67: 3.3M 1%; R_0603_1608Metric
R68: 1M 1%; R_0603_1608Metric
U6: AMS1117-3.3; SOT-223-3_TabPin2
U8: TPS61023DRLR; SOT-563
U9: TLV3012BIDBVR; SOT-23-6

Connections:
+3V3: C45.1, U6.2 (VO); also elsewhere on the board
+5V: C43.1, C44.1, C57.1, C58.1, R63.1, U6.3 (VI), U8.6; also elsewhere on the board
BOOST_EN: R67.2, R68.1, U8.2, U9.1
BOOST_FB: C58.2, R63.2, R64.1, U8.1
BOOST_SW: L5.2, U8.5
FCU_LBAT_ADC: C46.1, R15.2, R16.1; also elsewhere on the board
GND: C41.2, C42.2, C43.2, C44.2, C45.2, C46.2, C57.2, C59.2, C60.2, J14.2, NT1.1, R14.2, R16.2, R64.2, R66.2, R68.2, U6.1 (GND), U8.4, U9.2 (V-); also elsewhere on the board
GND_PWR: NT1.2; also elsewhere on the board
LBAT_PFET_G: Q10.1 (G), R14.1
UVLO_REF: U9.4 (-), U9.5 (Vref)
UVLO_SENSE: C60.1, R65.2, R66.1, R67.1, U9.3 (+)
VBAT_LOGIC: J15.1, Q10.2 (S)
VBAT_LOGIC_RAW: J14.1, Q10.3 (D)
VBAT_LOGIC_SW: C41.1, C42.1, C59.1, J15.2, L5.1, R15.1, R65.1, U8.3, U9.6 (V+)

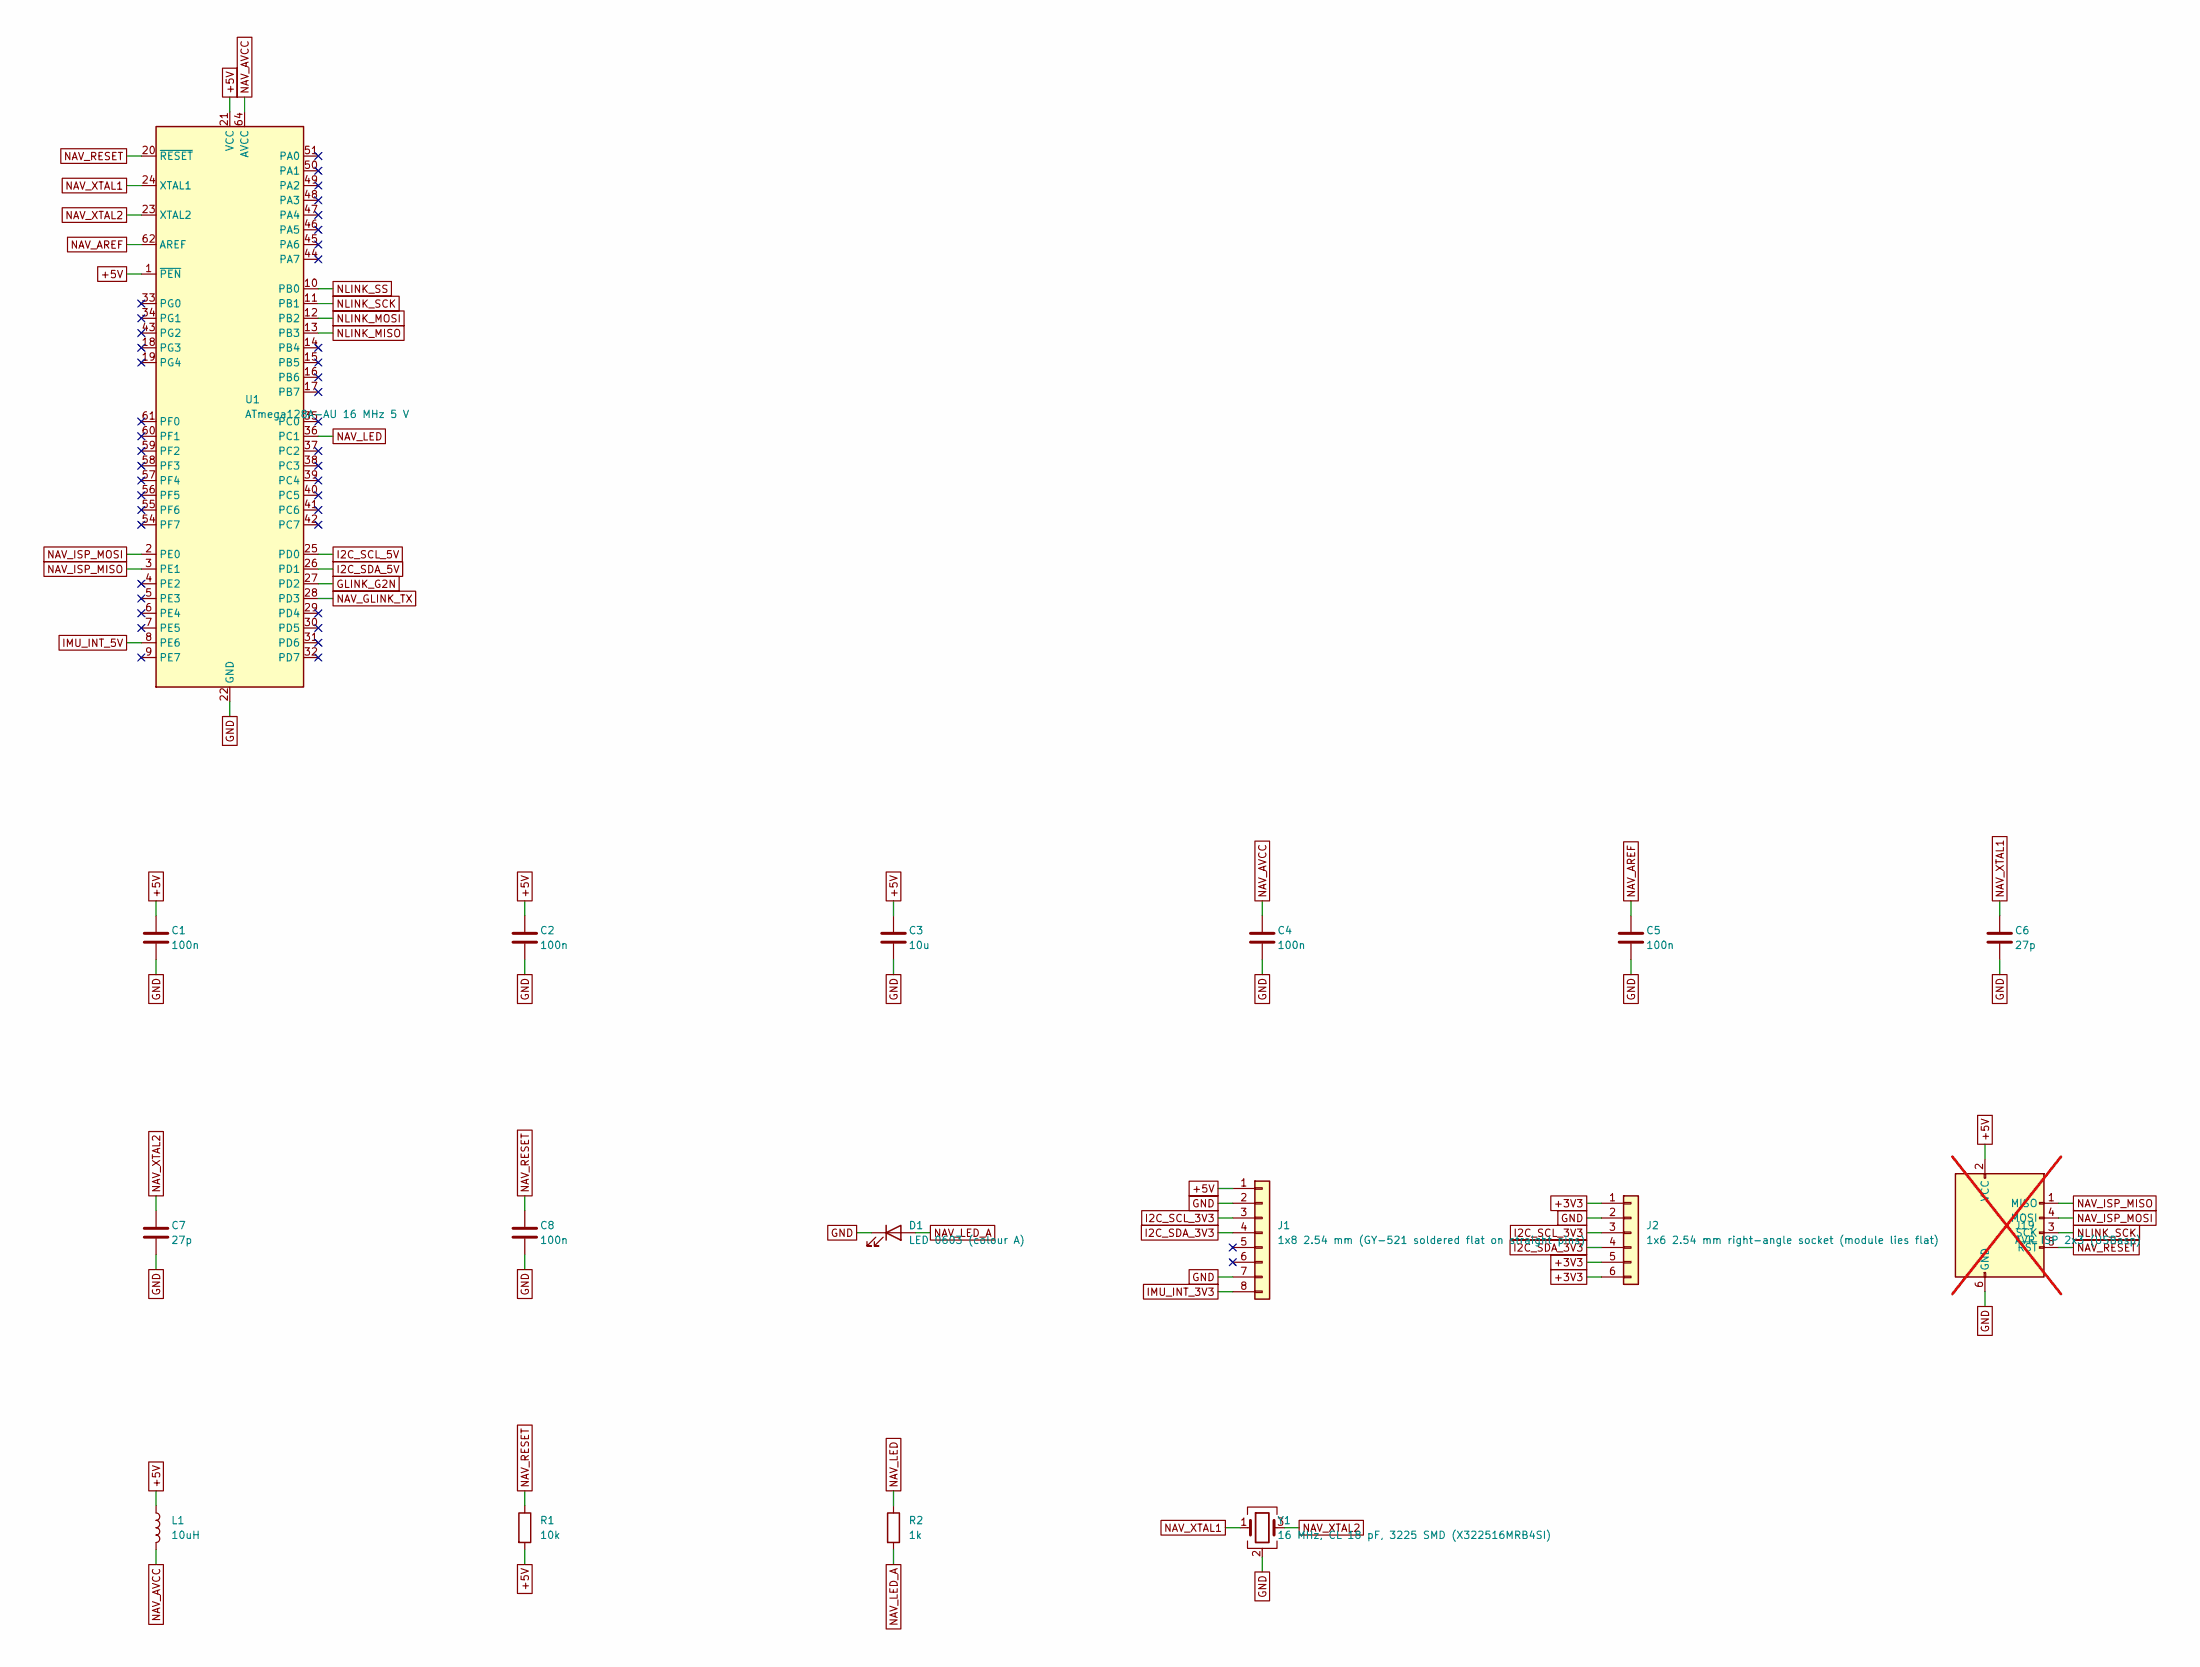
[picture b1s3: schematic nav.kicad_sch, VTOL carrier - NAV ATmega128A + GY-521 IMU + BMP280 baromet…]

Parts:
C1, C2, C4: 100n; C_0402_1005Metric
C3: 10u; C_0805_2012Metric
C5, C8: 100n; C_0603_1608Metric
C6, C7: 27p; C_0402_1005Metric
D1: LED 0603 (colour A); LED_0603_1608Metric
J1: 1x8 2.54 mm (GY-521 soldered flat on straight pin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; PinHeader_1x08_P2.54mm_Vertical
J2: 1x6 2.54 mm right-angle socket (module lies flat); PinSocket_1x06_P2.54mm_Horizontal
J19: AVR ISP 2x3 (USBasp); PinHeader_2x03_P2.54mm_Vertical; not fitted
L1: 10uH; L_0805_2012Metric
R1: 10k; R_0603_1608Metric
R2: 1k; R_0603_1608Metric
U1: ATmega128A-AU 16 MHz 5 V; TQFP-64_14x14mm_P0.8mm
Y1: 16 MHz, CL 18 pF, 3225 SMD (X322516MRB4SI); Crystal_SMD_3225-4Pin_3.2x2.5mm

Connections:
+3V3: J2.1, J2.5, J2.6; also elsewhere on the board
+5V: C1.1, C2.1, C3.1, J1.1, J19.2 (VCC), L1.1, R1.2, U1.1 (~PEN), U1.21 (VCC), U1.52 (VCC); also elsewhere on the board
GLINK_G2N: U1.27 (PD2); also elsewhere on the board
GND: C1.2, C2.2, C3.2, C4.2, C5.2, C6.2, C7.2, C8.2, D1.1 (K), J1.2, J1.7, J2.2, J19.6 (GND), U1.22 (GND), U1.53 (GND), U1.63 (GND), Y1.2 (G), Y1.4 (G); also elsewhere on the board
I2C_SCL_3V3: J1.3, J2.3; also elsewhere on the board
I2C_SCL_5V: U1.25 (PD0); also elsewhere on the board
I2C_SDA_3V3: J1.4, J2.4; also elsewhere on the board
I2C_SDA_5V: U1.26 (PD1); also elsewhere on the board
IMU_INT_3V3: J1.8; also elsewhere on the board
IMU_INT_5V: U1.8 (PE6); also elsewhere on the board
NAV_AREF: C5.1, U1.62 (AREF)
NAV_AVCC: C4.1, L1.2, U1.64 (AVCC)
NAV_GLINK_TX: U1.28 (PD3); also elsewhere on the board
NAV_ISP_MISO: J19.1 (MISO), U1.3 (PE1)
NAV_ISP_MOSI: J19.4 (MOSI), U1.2 (PE0)
NAV_LED: R2.1, U1.36 (PC1)
NAV_LED_A: D1.2 (A), R2.2
NAV_RESET: C8.1, J19.5 (~RST), R1.1, U1.20 (~RESET); also elsewhere on the board
NAV_XTAL1: C6.1, U1.24 (XTAL1), Y1.1
NAV_XTAL2: C7.1, U1.23 (XTAL2), Y1.3
NLINK_MISO: U1.13 (PB3); also elsewhere on the board
NLINK_MOSI: U1.12 (PB2); also elsewhere on the board
NLINK_SCK: J19.3 (SCK), U1.11 (PB1); also elsewhere on the board
NLINK_SS: U1.10 (PB0); also elsewhere on the board

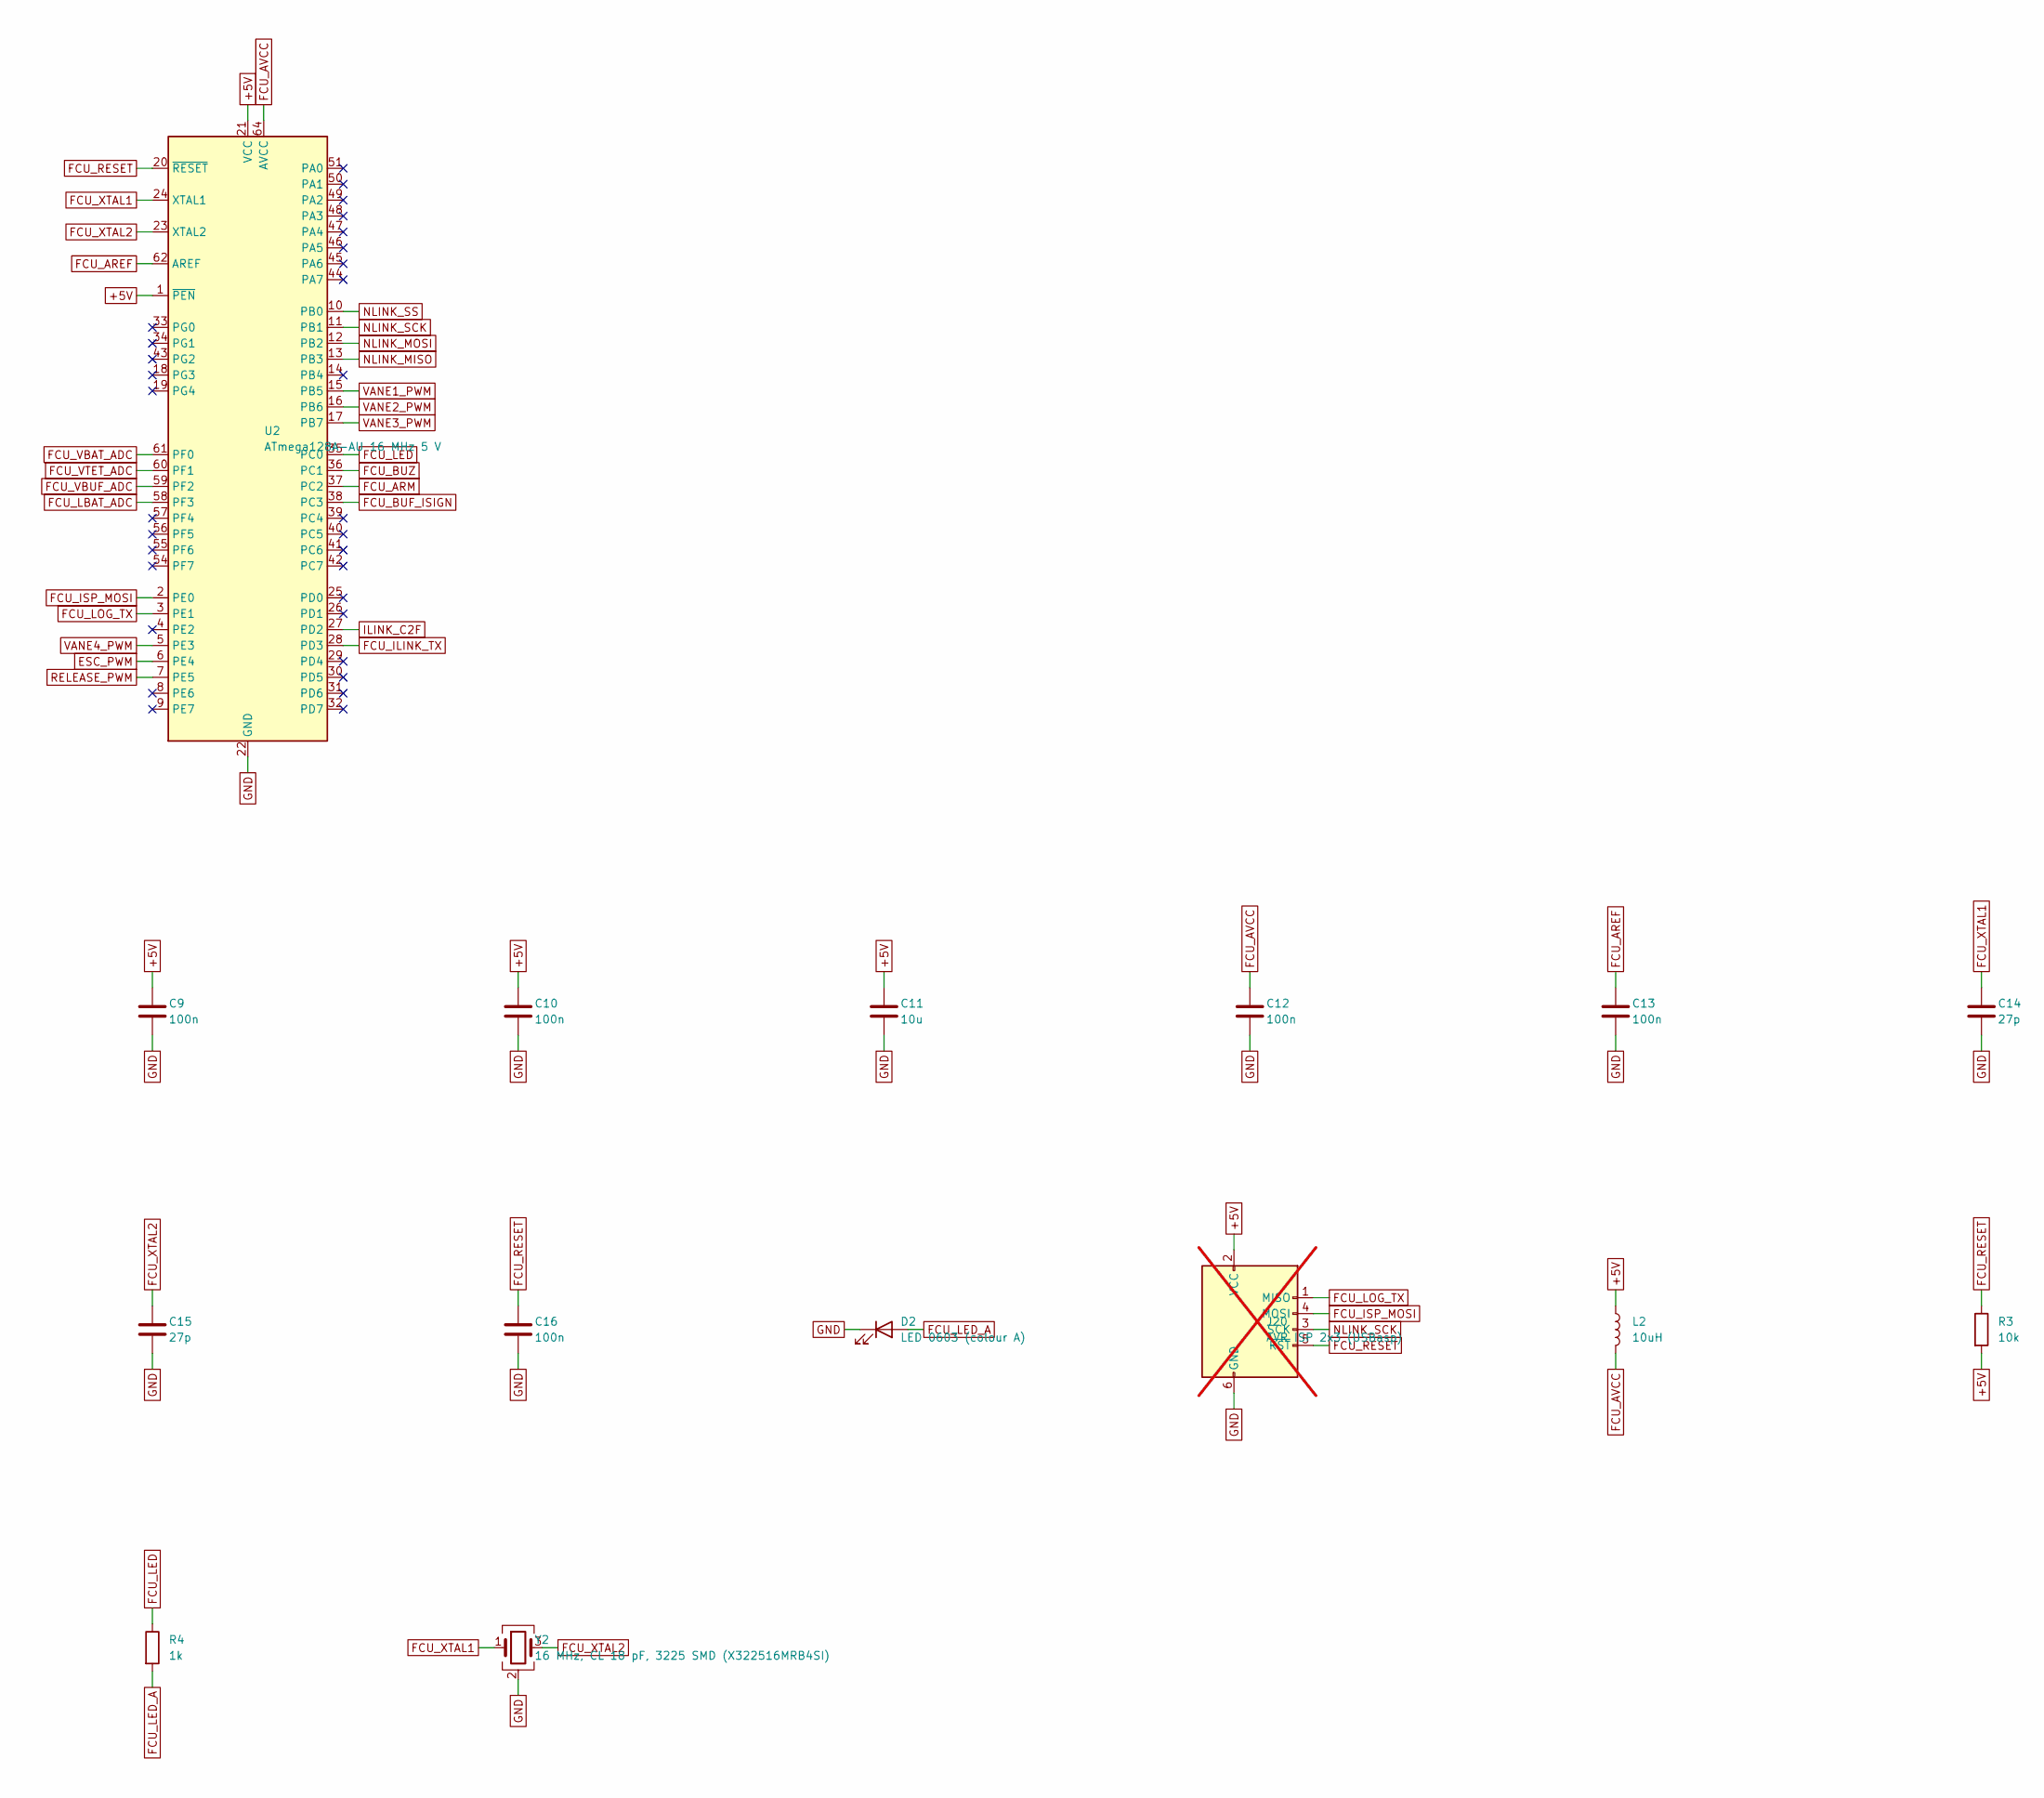
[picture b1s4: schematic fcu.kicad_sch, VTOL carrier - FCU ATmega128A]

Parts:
C9, C10, C12: 100n; C_0402_1005Metric
C11: 10u; C_0805_2012Metric
C13, C16: 100n; C_0603_1608Metric
C14, C15: 27p; C_0402_1005Metric
D2: LED 0603 (colour A); LED_0603_1608Metric
J20: AVR ISP 2x3 (USBasp); PinHeader_2x03_P2.54mm_Vertical; not fitted
L2: 10uH; L_0805_2012Metric
R3: 10k; R_0603_1608Metric
R4: 1k; R_0603_1608Metric
U2: ATmega128A-AU 16 MHz 5 V; TQFP-64_14x14mm_P0.8mm
Y2: 16 MHz, CL 18 pF, 3225 SMD (X322516MRB4SI); Crystal_SMD_3225-4Pin_3.2x2.5mm

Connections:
+5V: C9.1, C10.1, C11.1, J20.2 (VCC), L2.1, R3.2, U2.1 (~PEN), U2.21 (VCC), U2.52 (VCC); also elsewhere on the board
ESC_PWM: U2.6 (PE4); also elsewhere on the board
FCU_AREF: C13.1, U2.62 (AREF)
FCU_ARM: U2.37 (PC2); also elsewhere on the board
FCU_AVCC: C12.1, L2.2, U2.64 (AVCC)
FCU_BUF_ISIGN: U2.38 (PC3); also elsewhere on the board
FCU_BUZ: U2.36 (PC1); also elsewhere on the board
FCU_ILINK_TX: U2.28 (PD3); also elsewhere on the board
FCU_ISP_MOSI: J20.4 (MOSI), U2.2 (PE0)
FCU_LBAT_ADC: U2.58 (PF3); also elsewhere on the board
FCU_LED: R4.1, U2.35 (PC0)
FCU_LED_A: D2.2 (A), R4.2
FCU_LOG_TX: J20.1 (MISO), U2.3 (PE1); also elsewhere on the board
FCU_RESET: C16.1, J20.5 (~RST), R3.1, U2.20 (~RESET); also elsewhere on the board
FCU_VBAT_ADC: U2.61 (PF0); also elsewhere on the board
FCU_VBUF_ADC: U2.59 (PF2); also elsewhere on the board
FCU_VTET_ADC: U2.60 (PF1); also elsewhere on the board
FCU_XTAL1: C14.1, U2.24 (XTAL1), Y2.1
FCU_XTAL2: C15.1, U2.23 (XTAL2), Y2.3
GND: C9.2, C10.2, C11.2, C12.2, C13.2, C14.2, C15.2, C16.2, D2.1 (K), J20.6 (GND), U2.22 (GND), U2.53 (GND), U2.63 (GND), Y2.2 (G), Y2.4 (G); also elsewhere on the board
ILINK_C2F: U2.27 (PD2); also elsewhere on the board
NLINK_MISO: U2.13 (PB3); also elsewhere on the board
NLINK_MOSI: U2.12 (PB2); also elsewhere on the board
NLINK_SCK: J20.3 (SCK), U2.11 (PB1); also elsewhere on the board
NLINK_SS: U2.10 (PB0); also elsewhere on the board
RELEASE_PWM: U2.7 (PE5); also elsewhere on the board
VANE1_PWM: U2.15 (PB5); also elsewhere on the board
VANE2_PWM: U2.16 (PB6); also elsewhere on the board
VANE3_PWM: U2.17 (PB7); also elsewhere on the board
VANE4_PWM: U2.5 (PE3); also elsewhere on the board

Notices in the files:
README.md:
License: CC BY-NC 4.0
